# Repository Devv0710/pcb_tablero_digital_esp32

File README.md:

Este documento detalla las especificaciones técnicas y decisiones de diseño de hardware para la PCB de control de un tablero marcador digital. El sistema está basado en el microcontrolador **ESP8266 (Wemos D1 Mini)** y está diseñado para gestionar tiras LED direccionables de alta potencia y periféricos inductivos.

> **[IMAGEN 1: VISTA GENERAL DE LA PCB]**
>

## 1. Arquitectura de Distribución de Potencia

El diseño gestiona dos rieles de alimentación independientes para evitar que el ruido de los actuadores y la carga de los LEDs interfieran con la estabilidad del microcontrolador.

> **[IMAGEN 2: DIAGRAMA DE BLOQUES DE POTENCIA U ORDENACIÓN FÍSICA]**
>
>

### Rail de Potencia Principal (5V)
* **Carga de LEDs:** El sistema controla 13 dígitos. El consumo máximo teórico es de **7.6A** (blanco al 100% de brillo), con un consumo típico de **400mA** por dígito en operación estándar.
* **Plano de Cobre:** Para soportar esta corriente sin caídas de tensión significativas (IR Drop), se utilizó un **plano de potencia de cobre** en la capa superior (Top Layer).
* **Protección:** Un fusible de acción rápida de **10A** (**F1**) protege la integridad de las pistas y componentes ante cortocircuitos en las tiras externas.

### Rail de Periféricos (12V)
* **Función:** Alimentación exclusiva para una bocina externa de alta potencia.
* **Consumo:** Optimizado para cargas menores a **1A**.
* **Control Electrónico:** Implementado mediante un MOSFET N-Channel **AO3400A**. 
* **Protección Inductiva:** Se incluyó un diodo de libre circulación (**1N4007**) en paralelo con la carga para suprimir los picos de fuerza contraelectromotriz al conmutar la bocina.  

## 2. Diseño de la PCB y Stackup

La placa se diseñó en **2 capas** con una estrategia de baja impedancia para manejar las altas corrientes involucradas.

### Capas y Planos (Copper Pours)

* **Capa Inferior (Bottom Layer - GND):** Utilizada íntegramente como un plano de masa continuo.
* **Capa Superior (Top Layer - 5V):** Aloja las señales y un plano de alimentación robusto para los 5V.
  
> **[IMAGEN 3: VISUALIZACIÓN DE LOS PLANOS DE COBRE EN KICAD]**
>
>

### Filtrado de Transitorios
Se implementó una red de desacoplo masiva con una capacitancia total cercana a los **10,000 uF** (incluyendo capacitores electrolíticos de **2200uF** y **1000uF**) para estabilizar el riel de 5V ante los cambios rápidos de estado de los LEDs.
## 3. Integridad de Señal y Lógica de Control

Para asegurar la comunicación fiable con los 13 dígitos de LEDs **WS2813**, se implementaron las siguientes etapas:

### Conversión de Niveles Lógicos (Level Shifting)
Dado que el ESP8266 opera a 3.3V y los LEDs requieren un umbral lógico cercano a 5V para evitar errores de datos, se incorporó un buffer de alta velocidad **74AHCT244**. Este componente asegura que los pulsos de datos tengan flancos de subida y bajada limpios y con la amplitud necesaria (5V).

### Terminación de Línea
Cada salida de datos hacia los dígitos incluye una resistencia serie de **330 Ohm**. Esto ayuda a:
* Reducir el *ringing* y las reflexiones en los cables de conexión.
* Proteger los pines de salida del buffer ante transitorios.

## 4. Selección de Componentes y Justificación

| Componente | Función | Justificación Técnica |
| :--- | :--- | :--- |
| **WS2813** | LEDs RGB | Posee un pin de **Backup Data**. Si un LED falla, la señal no se interrumpe. |
| **AO3400A** | MOSFET de Control | Baja resistencia $R_{DS(on)}$ para minimizar pérdidas térmicas en el control de la bocina (Carga < 1A). |
| **74AHCT244** | Level Shifter | Buffer de grado industrial para compatibilidad entre lógica CMOS de 3.3V y TTL de 5V. |

### Especificaciones de los LEDs (según Datasheet)
* **Corriente Quiescente:** < 0.6mA.
* **Intensidad Lumínica:** Rojo (380-600 mcd), Verde (1050-1500 mcd), Azul (270-400 mcd) a 16mA.
* **Longitud de onda:** Rojo (623nm), Verde (520nm), Azul (471nm).

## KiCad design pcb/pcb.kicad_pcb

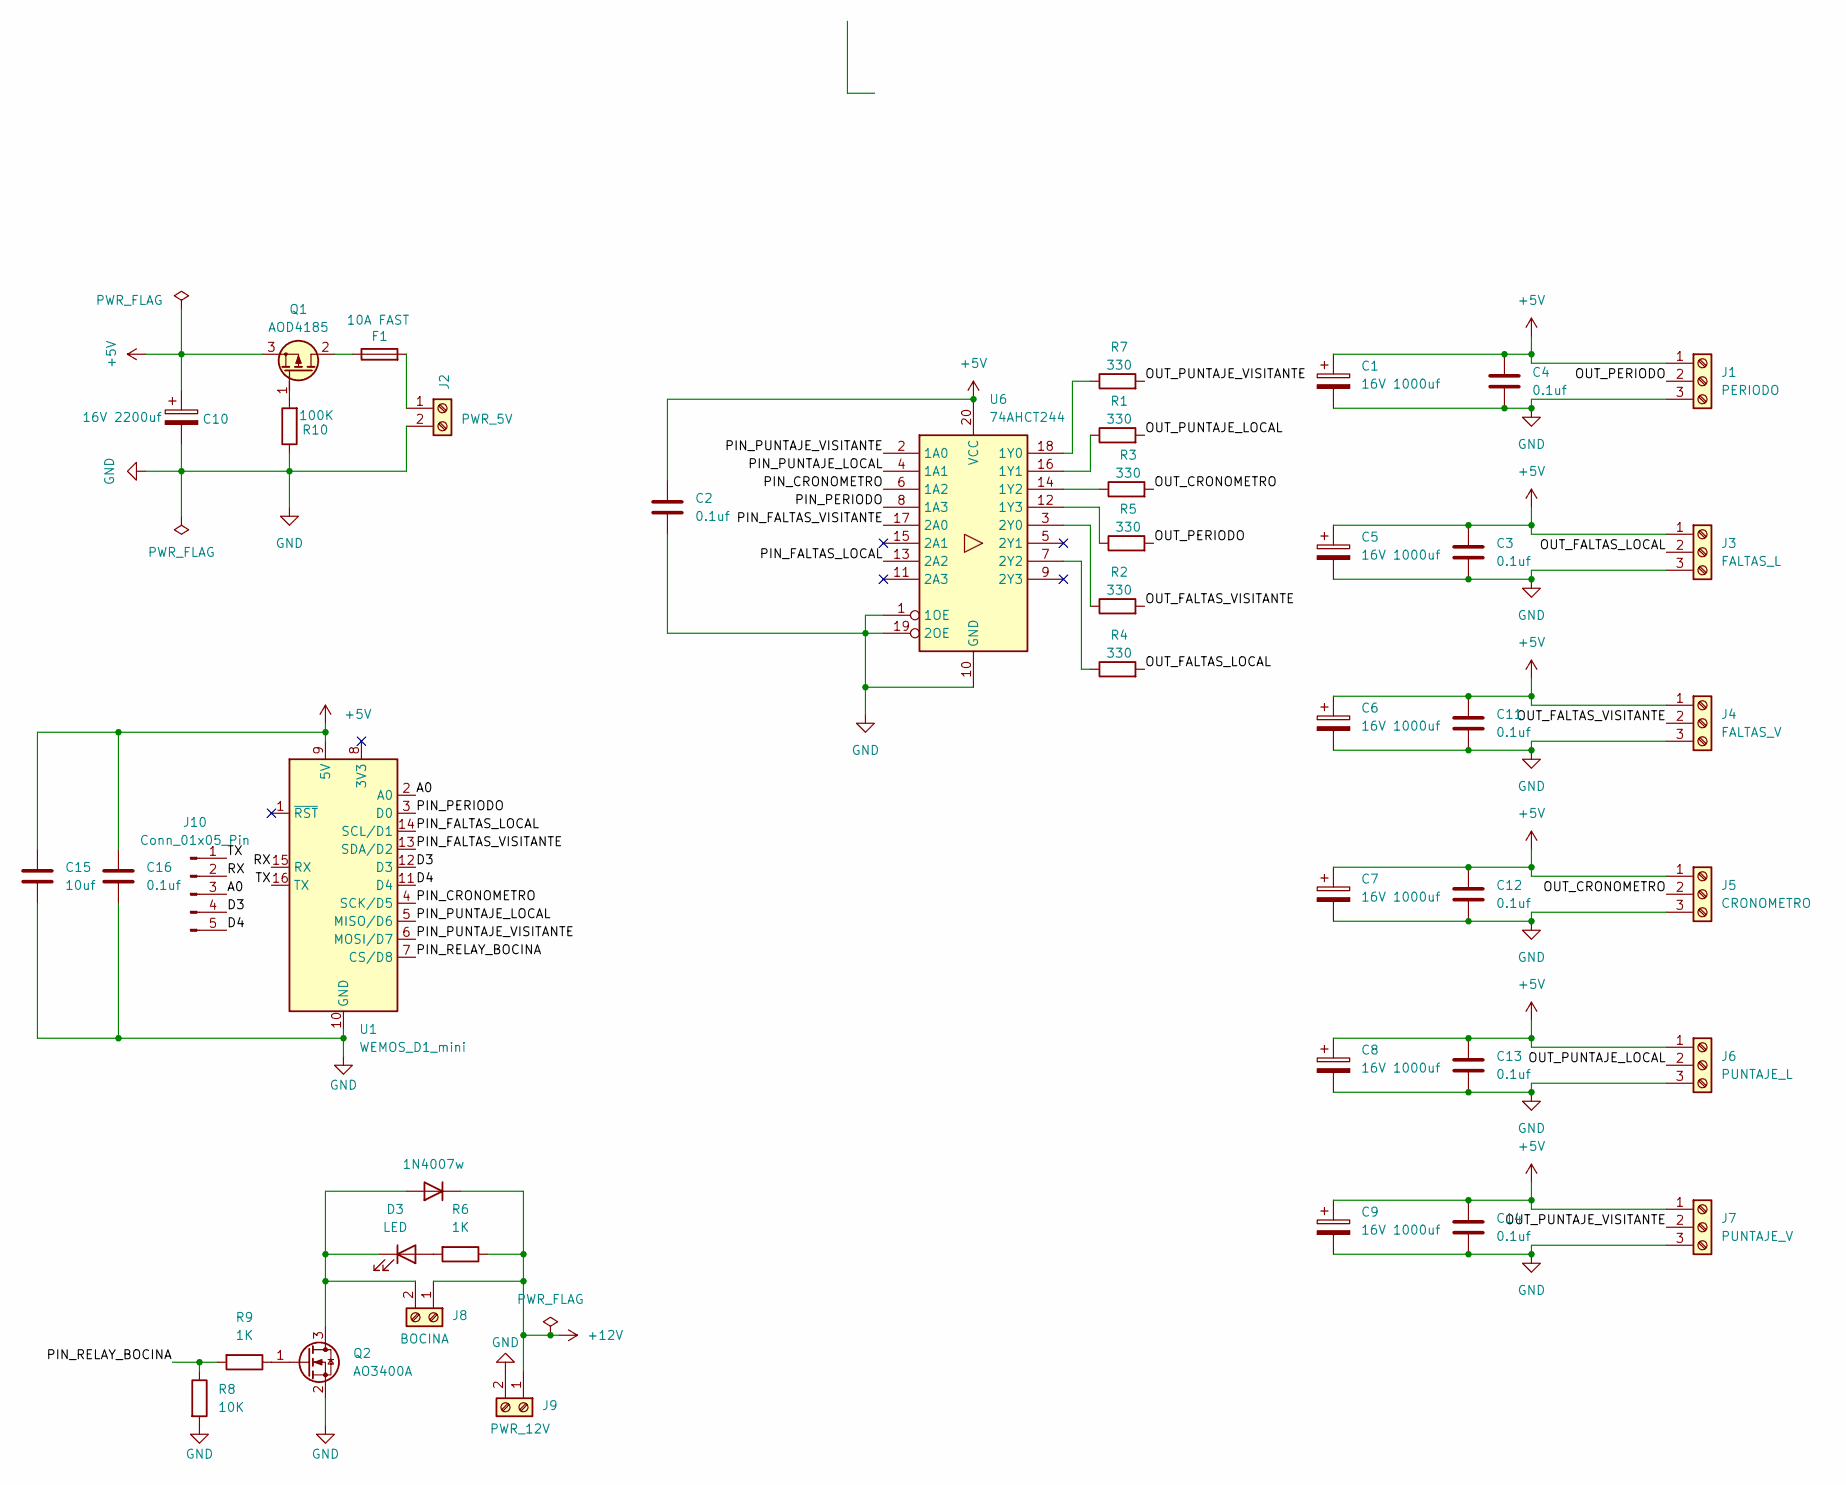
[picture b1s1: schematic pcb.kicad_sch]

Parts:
C1, C5, C6, C7, C8, C9: 16V 1000uf; CP_Radial_D10.0mm_P5.00mm
C2, C3, C4, C11, C12, C13, C14, C16: 0.1uf; C_0805_2012Metric
C10: 16V 2200uf; CP_Radial_D10.0mm_P5.00mm
C15: 10uf; C_0805_2012Metric
D2: 1N4007w; D_SOD-123
D3: LED; LED_0805_2012Metric_Pad1.15x1.40mm_HandSolder
F1: 10A FAST; Fuse_0603_1608Metric_Pad1.05x0.95mm_HandSolder
J1: PERIODO; TerminalBlock_Altech_AK300-3_P5.00mm
J2: PWR_5V; TerminalBlock_Altech_AK300-2_P5.00mm
J3: FALTAS_L; TerminalBlock_Altech_AK300-3_P5.00mm
J4: FALTAS_V; TerminalBlock_Altech_AK300-3_P5.00mm
J5: CRONOMETRO; TerminalBlock_Altech_AK300-3_P5.00mm
J6: PUNTAJE_L; TerminalBlock_Altech_AK300-3_P5.00mm
J7: PUNTAJE_V; TerminalBlock_Altech_AK300-3_P5.00mm
J8: BOCINA; TerminalBlock_Altech_AK300-2_P5.00mm
J9: PWR_12V; TerminalBlock_Altech_AK300-2_P5.00mm
J10: Conn_01x05_Pin; PinHeader_1x05_P2.54mm_Vertical
Q1: AOD4185; TO-252-2
Q2: AO3400A; SOT-23
R1, R2, R3, R4, R5, R7: 330; R_1206_3216Metric_Pad1.30x1.75mm_HandSolder
R6, R9: 1K; R_1206_3216Metric_Pad1.30x1.75mm_HandSolder
R8: 10K; R_1206_3216Metric_Pad1.30x1.75mm_HandSolder
R10: 100K; R_1206_3216Metric_Pad1.30x1.75mm_HandSolder
U1: WEMOS_D1_mini; WEMOS_D1_mini_light
U6: 74AHCT244; SO-20_12.8x7.5mm_P1.27mm

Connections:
+5V: C1.1, C2.1, C3.1, C4.1, C5.1, C6.1, C7.1, C8.1, C9.1, C10.1, C11.1, C12.1, C13.1, C14.1, C15.1, C16.1, J1.1, J3.1, J4.1, J5.1, J6.1, J7.1, Q1.3 (S), U1.9 (5V), U6.20 (VCC)
+12V: D2.1 (K), J8.1, J9.1, R6.1
/A0: J10.3, U1.2 (A0)
/D3: J10.4, U1.12 (D3)
/D4: J10.5, U1.11 (D4)
/OUT_CRONOMETRO: J5.2, R3.2
/OUT_FALTAS_LOCAL: J3.2, R4.2
/OUT_FALTAS_VISITANTE: J4.2, R2.2
/OUT_PERIODO: J1.2, R5.2
/OUT_PUNTAJE_LOCAL: J6.2, R1.2
/OUT_PUNTAJE_VISITANTE: J7.2, R7.2
/PIN_CRONOMETRO: U1.4 (SCK/D5), U6.6 (1A2)
/PIN_FALTAS_LOCAL: U1.14 (SCL/D1), U6.13 (2A2)
/PIN_FALTAS_VISITANTE: U1.13 (SDA/D2), U6.17 (2A0)
/PIN_PERIODO: U1.3 (D0), U6.8 (1A3)
/PIN_PUNTAJE_LOCAL: U1.5 (MISO/D6), U6.4 (1A1)
/PIN_PUNTAJE_VISITANTE: U1.6 (MOSI/D7), U6.2 (1A0)
/PIN_RELAY_BOCINA: R8.1, R9.2, U1.7 (CS/D8)
/RX: J10.2, U1.15 (RX)
/TX: J10.1, U1.16 (TX)
GND: C1.2, C2.2, C3.2, C4.2, C5.2, C6.2, C7.2, C8.2, C9.2, C10.2, C11.2, C12.2, C13.2, C14.2, C15.2, C16.2, J1.3, J2.2, J3.3, J4.3, J5.3, J6.3, J7.3, J9.2, Q2.2 (S), R8.2, R10.1, U1.10 (GND), U6.1 (1OE), U6.10 (GND), U6.19 (2OE)
unnamed: D2.2 (A), D3.1 (K), J8.2, Q2.3 (D)
unnamed: D3.2 (A), R6.2
unnamed: F1.2, J2.1
unnamed: F1.1, Q1.2 (D)
unnamed: Q1.1 (G), R10.2
unnamed: Q2.1 (G), R9.1
unnamed: R7.1, U6.18 (1Y0)
unnamed: R1.1, U6.16 (1Y1)
unnamed: R3.1, U6.14 (1Y2)
unnamed: R5.1, U6.12 (1Y3)
unnamed: R2.1, U6.3 (2Y0)
unnamed: R4.1, U6.7 (2Y2)

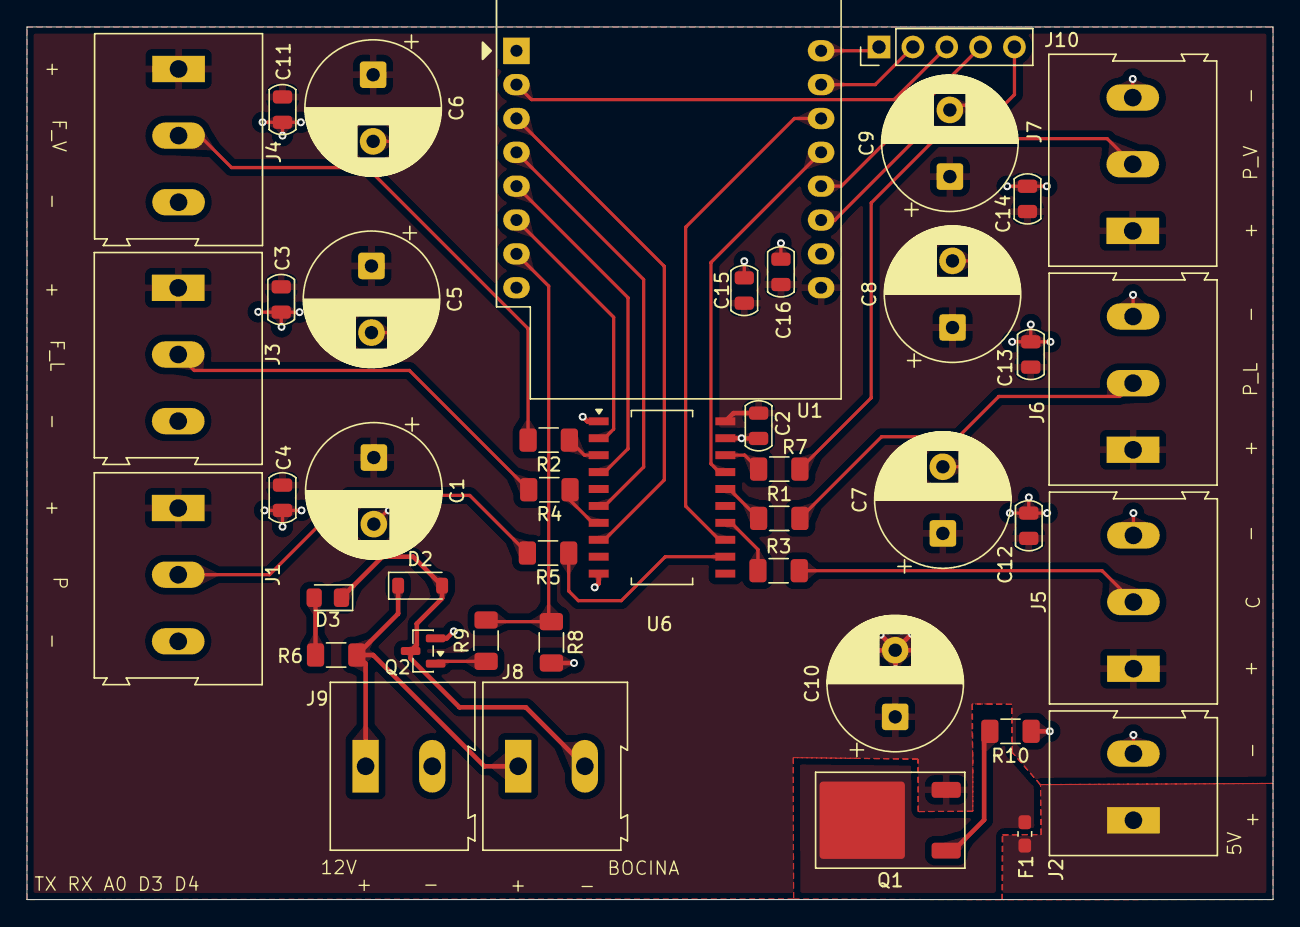
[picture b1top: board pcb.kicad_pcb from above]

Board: 2 copper layers, 93.5 x 65.5 mm, 43 parts (0 on the bottom side), 33 nets.

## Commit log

2025-11-14 v1, con relay integrado, proteciones para polaridad inversa y fusible.
2025-12-22 refactor: optimize power efficiency and reduce PCB footprint
    Replace series protection diode with P-Channel MOSFET (AOD4185) to minimize voltage drop.
    Migrate from ESP32-DevKitC to Wemos D1 Mini (ESP8266) for cost and size reduction.
    Replace mechanical relay with N-Channel MOSFET for silent and efficient buzzer control.
    Update schematics and PCB layout accordingly.
2025-12-29 feat(pcb): Actualizar diseño y eliminar esquemático obsoleto
    - Reemplaza conector de 6 por 5 pines en el esquemático.
    - Regenera el layout del PCB y actualiza el ruteado.
    - Añade nuevo ancho de pista de 0.35mm en la configuración.
    - Elimina el archivo de esquemático no utilizado 'untitled.kicad_sch'.
2025-12-30 Agregar especificaciones técnicas de la PCB
    Este documento detalla las especificaciones técnicas y decisiones de diseño de hardware para la PCB de control de un tablero marcador digital basado en el microcontrolador ESP8266.
